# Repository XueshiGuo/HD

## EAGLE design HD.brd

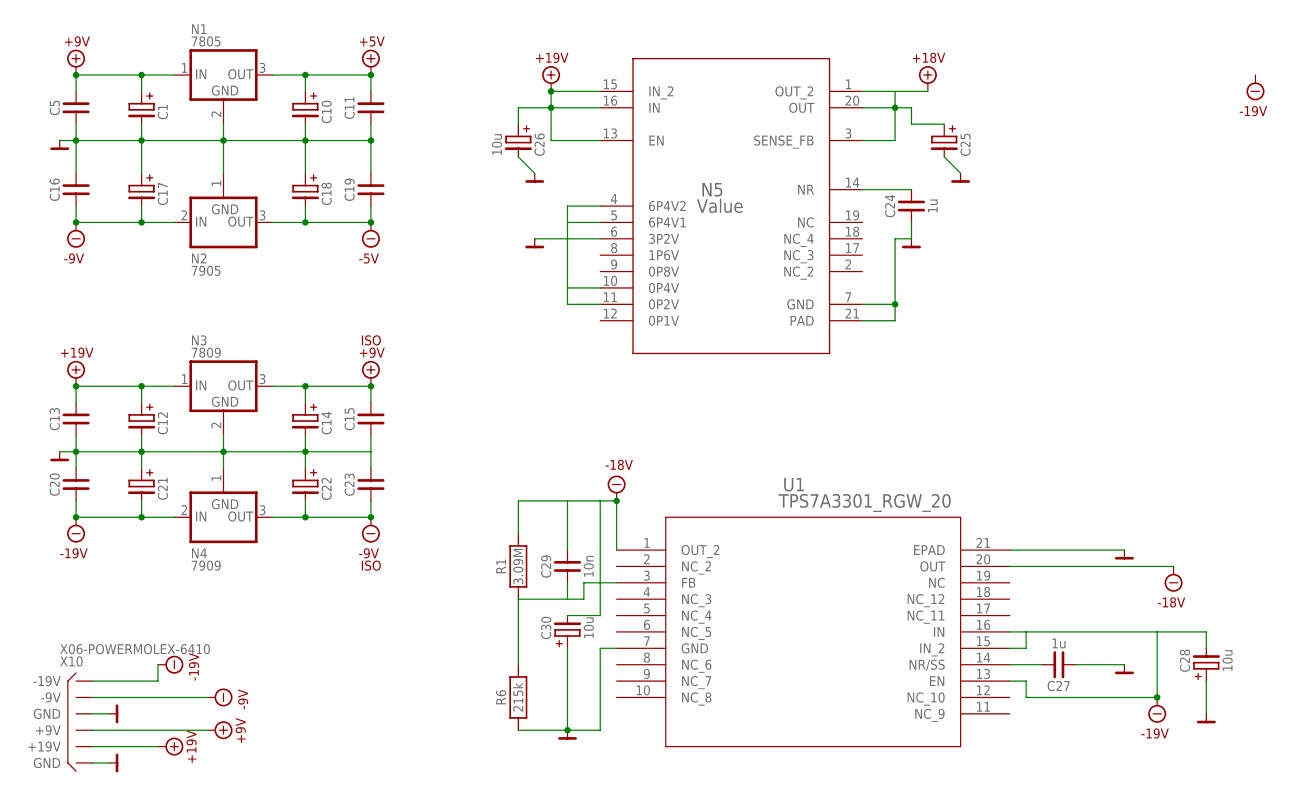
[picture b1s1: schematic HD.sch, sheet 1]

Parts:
C1, C10, C12, C14, C17, C18, C21, C22, C25: CEC
C5, C11, C13, C15, C16, C19, C20, C23: C0805
C24, C27: 1u; C0805
C26, C28, C30: 10u; CEC
C29: 10n; C0805
N1: 7805; TO252
N2: 7905; TO252
N3: 7809; TO252
N4: 7909; TO252
N5: Value; RGW0020A
R1: 3.09M; R0805
R6: 215k; R0805
U1: TPS7A3301_RGW_20; RGW0020A
X10: X06-POWERMOLEX-6410; X06-MOLEX-6410

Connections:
+5V: C10.+, C11.2, N1.3 (OUT); also elsewhere on the board
+9V: C1.+, C5.1, N1.1 (IN), X10.P$4 (+9V)
+9VISO: C14.+, C15.2, N3.3 (OUT); also elsewhere on the board
+18V: C25.+, N5.1 (OUT_2), N5.3 (SENSE_FB), N5.20 (OUT); also elsewhere on the board
+19V: C12.+, C13.1, C26.+, N3.1 (IN), N5.13 (EN), N5.15 (IN_2), N5.16 (IN), X10.P$5 (+19V)
-5V: C18.-, C19.1, N2.3 (OUT); also elsewhere on the board
-9V: C16.2, C17.-, N2.2 (IN), X10.P$2 (-9V)
-9VISO: C22.-, C23.1, N4.3 (OUT); also elsewhere on the board
-18V: C29.2, C30.-, R1.2, U1.1 (OUT_2), U1.20 (OUT); also elsewhere on the board
-19V: C20.2, C21.-, C28.-, N4.2 (IN), U1.13 (EN), U1.15 (IN_2), U1.16 (IN), X10.P$1 (-19V)
GND: C1.-, C5.2, C10.-, C11.1, C12.-, C13.2, C14.-, C15.1, C16.1, C17.+, C18.+, C19.2, C20.1, C21.+, C22.+, C23.2, C24.1, C25.-, C26.-, C27.1, C28.+, C30.+, N1.2 (GND), N2.1 (GND), N3.2 (GND), N4.1 (GND), N5.4 (6P4V2), N5.5 (6P4V1), N5.6 (3P2V), N5.7 (GND), N5.10 (0P4V), N5.11 (0P2V), N5.21 (PAD), R6.1, U1.7 (GND), U1.21 (EPAD), X10.P$3 (GND), X10.P$6 (GND); also elsewhere on the board
unnamed: C24.2, N5.14 (NR)
unnamed: C27.2, U1.14 (NR/SS)
unnamed: C29.1, R1.1, R6.2, U1.3 (FB)

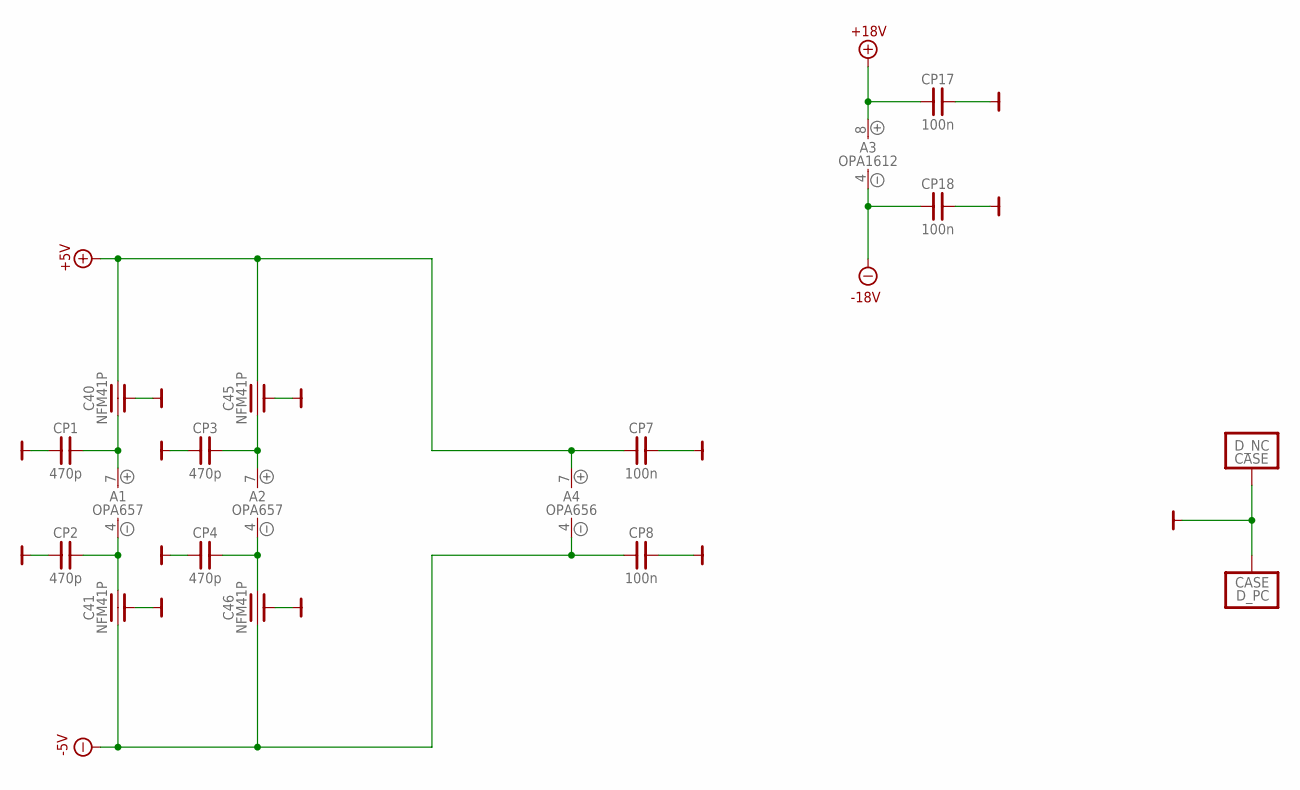
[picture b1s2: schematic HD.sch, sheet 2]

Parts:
A1, A2: OPA657; SO08
A3: OPA1612; SO08
A4: OPA656; SO08
C40, C41, C45, C46: NFM41P; CF-NFM41P
CP1, CP2, CP3, CP4: 470p; C0603
CP7, CP8, CP17, CP18: 100n; C0603
D_N: 0.2pF; STO5P
D_P: 0.2pF; STO5P

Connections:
+5V: A4.7 (V+), C40.2, C45.2, CP7.1; also elsewhere on the board
+18V: A3.8 (V+), CP17.1; also elsewhere on the board
-5V: A4.4 (V-), C41.1, C46.1, CP8.1; also elsewhere on the board
-18V: A3.4 (V-), CP18.1; also elsewhere on the board
GND: C40.GND, C41.GND, C45.GND, C46.GND, CP1.1, CP2.1, CP3.1, CP4.1, CP7.2, CP8.2, CP17.2, CP18.2, D_N.3 (CASE), D_P.3 (CASE); also elsewhere on the board
unnamed: A1.4 (V-), C41.2, CP2.2
unnamed: A1.7 (V+), C40.1, CP1.2
unnamed: A2.4 (V-), C46.2, CP4.2
unnamed: A2.7 (V+), C45.1, CP3.2

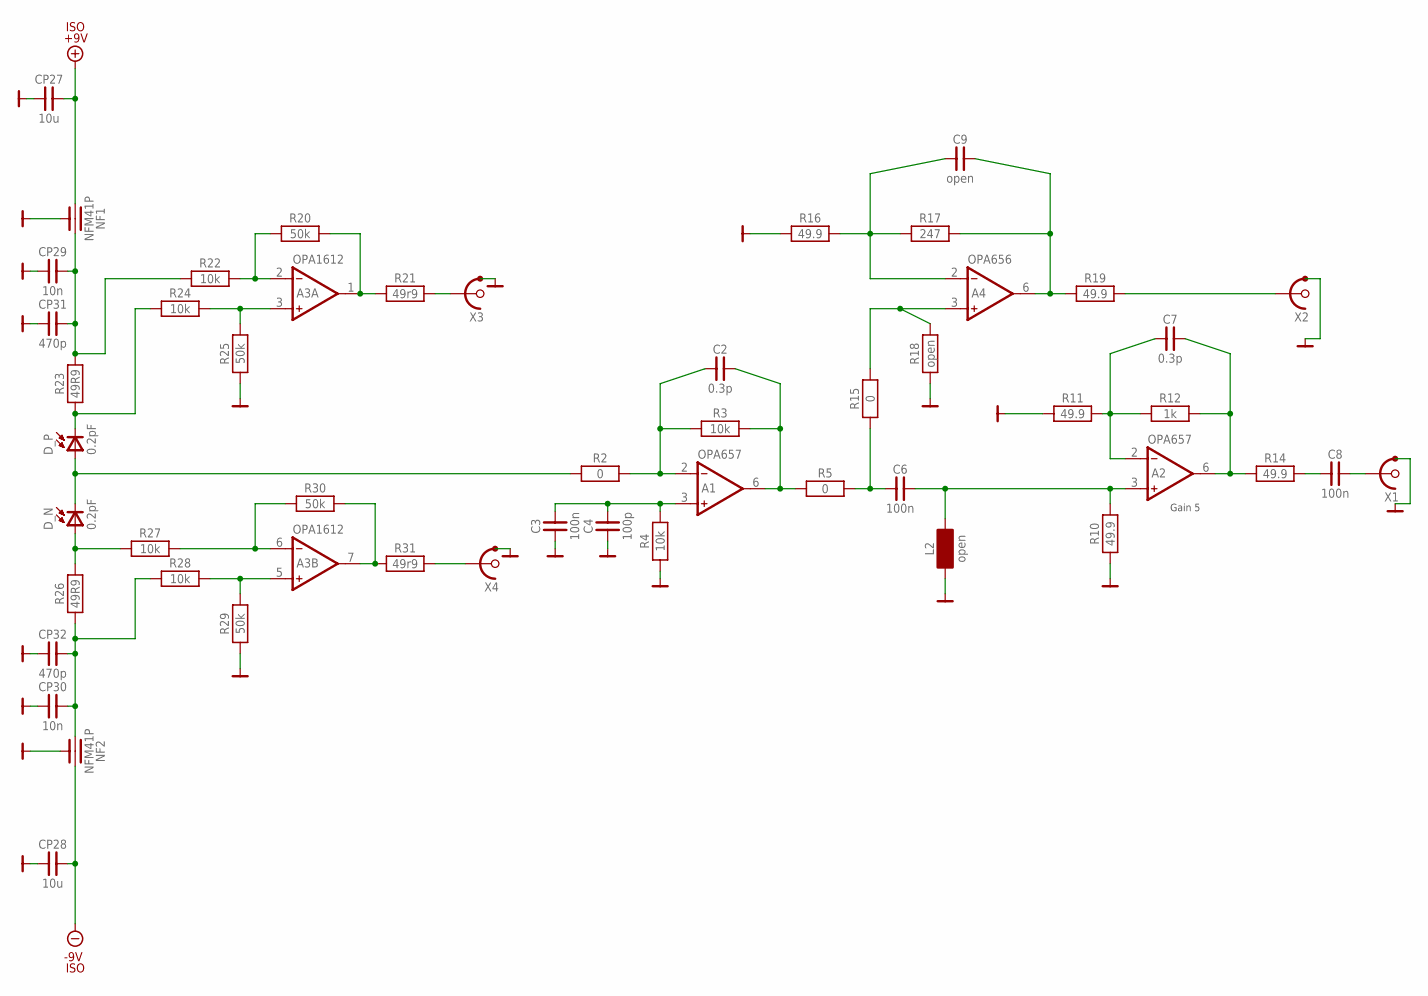
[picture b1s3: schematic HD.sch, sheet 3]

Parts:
A1, A2: OPA657; SO08
A3: OPA1612; SO08
A4: OPA656; SO08
C2, C7: 0.3p; C0603
C3, C6, C8: 100n; C0603
C4: 100p; C0603
C9: open; C0603
CP27, CP28: 10u; C1206
CP29, CP30: 10n; C0805
CP31, CP32: 470p; C0805
D_N: 0.2pF; STO5P
D_P: 0.2pF; STO5P
L2: open; L0603
NF1, NF2: NFM41P; CF-NFM41P
R2, R5: 0; R0603
R3, R4, R22, R24, R27, R28: 10k; R0603
R10, R11, R14, R16, R19: 49.9; R0603
R12: 1k; R0603
R15: 0; R0805
R17: 247; R0603
R18: open; R0603
R20, R25, R29, R30: 50k; R0603
R21, R31: 49r9; R0603
R23, R26: 49R9; R0603
X1, X2, X3, X4: XS01-PCB; XS01-UFL

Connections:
+9VISO: CP27.2, NF1.1; also elsewhere on the board
-9VISO: CP28.2, NF2.2; also elsewhere on the board
GND: C3.1, C4.1, CP27.1, CP28.1, CP29.1, CP30.1, CP31.1, CP32.1, L2.1, NF1.GND, NF2.GND, R4.1, R10.1, R11.1, R16.1, R18.1, R25.1, R29.1, X1.GND1 (GND), X1.GND2 (GND), X2.GND1 (GND), X2.GND2 (GND), X3.GND1 (GND), X3.GND2 (GND), X4.GND1 (GND), X4.GND2 (GND); also elsewhere on the board
unnamed: CP29.2, CP31.2, NF1.2, R22.1, R23.2
unnamed: A2.2 (IN-), C7.1, R11.2, R12.1
unnamed: A1.2 (IN-), C2.1, R2.2, R3.1
unnamed: A4.6 (OUT), C9.2, R17.2, R19.1
unnamed: C6.1, R5.2, R15.1
unnamed: A2.6 (OUT), C7.2, R12.2, R14.1
unnamed: A4.3 (IN+), R15.2, R18.2
unnamed: C8.1, R14.2
unnamed: A1.3 (IN+), C3.2, C4.2, R4.2
unnamed: C8.2, X1.SIG
unnamed: D_N.2 (C), D_P.1 (A), R2.1
unnamed: A4.2 (IN-), C9.1, R16.2, R17.1
unnamed: R19.2, X2.SIG
unnamed: A3.2 (IN-), R20.1, R22.2
unnamed: A3.1 (OUT), R20.2, R21.1
unnamed: R21.2, X3.SIG
unnamed: D_P.2 (C), R23.1, R24.1
unnamed: D_N.1 (A), R26.2, R27.1
unnamed: R31.2, X4.SIG
unnamed: A3.3 (IN+), R24.2, R25.2
unnamed: CP30.2, CP32.2, NF2.1, R26.1, R28.1
unnamed: A3.6 (IN-), R27.2, R30.1
unnamed: A3.5 (IN+), R28.2, R29.2
unnamed: A3.7 (OUT), R30.2, R31.1
unnamed: A1.6 (OUT), C2.2, R3.2, R5.1
RF: A2.3 (IN+), C6.2, L2.2, R10.2

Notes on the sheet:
Gain 5

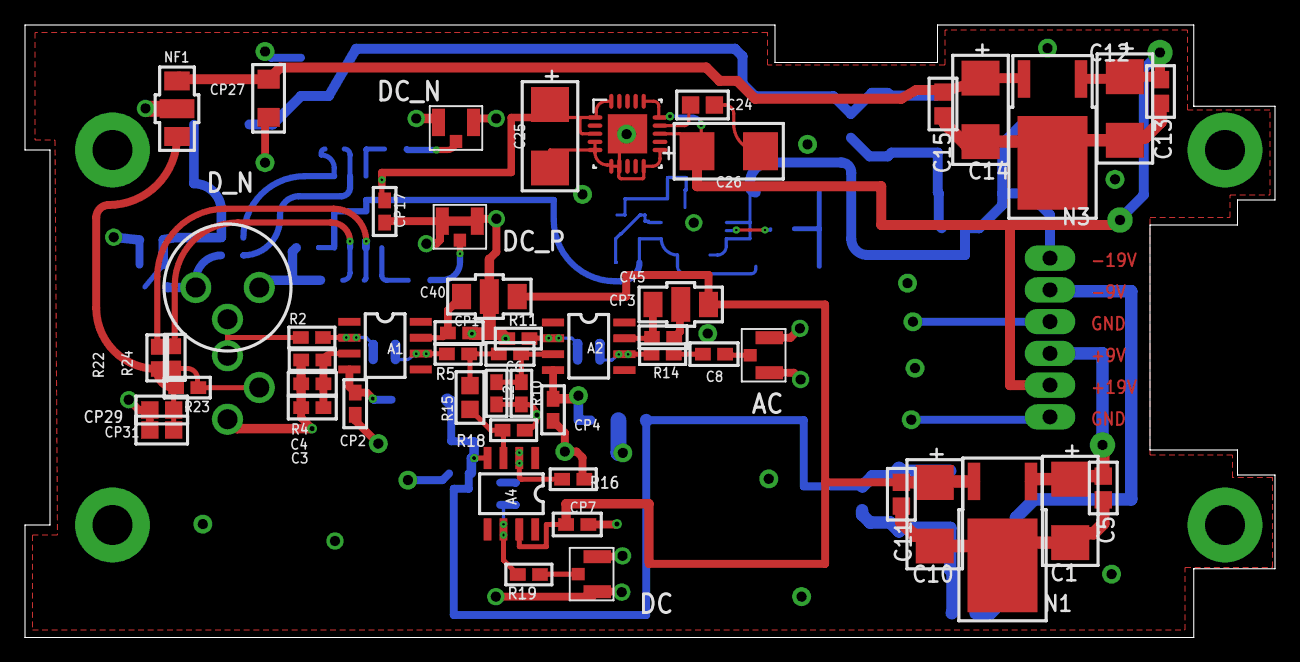
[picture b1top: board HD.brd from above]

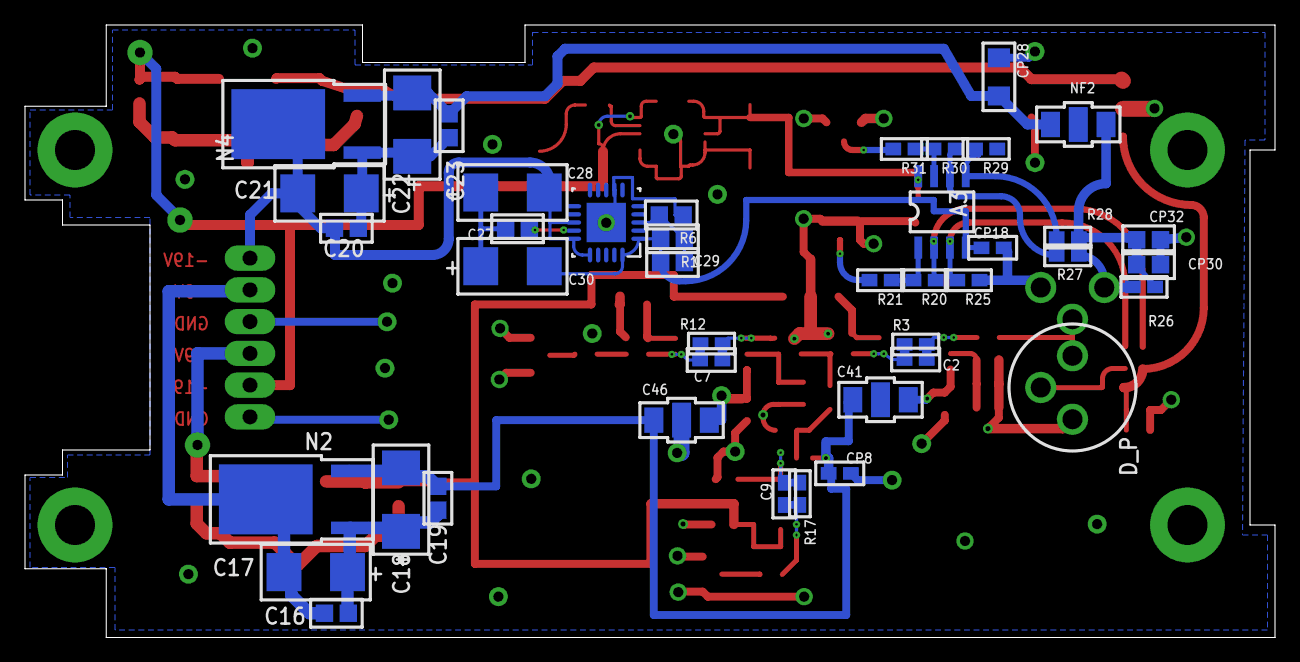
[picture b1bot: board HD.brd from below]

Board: 2 copper layers, 100.0 x 49.0 mm, 95 parts (42 on the bottom side), 44 nets.

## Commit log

2019-12-24 init.
